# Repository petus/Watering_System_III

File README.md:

# Watering_System_III
Watering system with ESP8266 (ESP12E)

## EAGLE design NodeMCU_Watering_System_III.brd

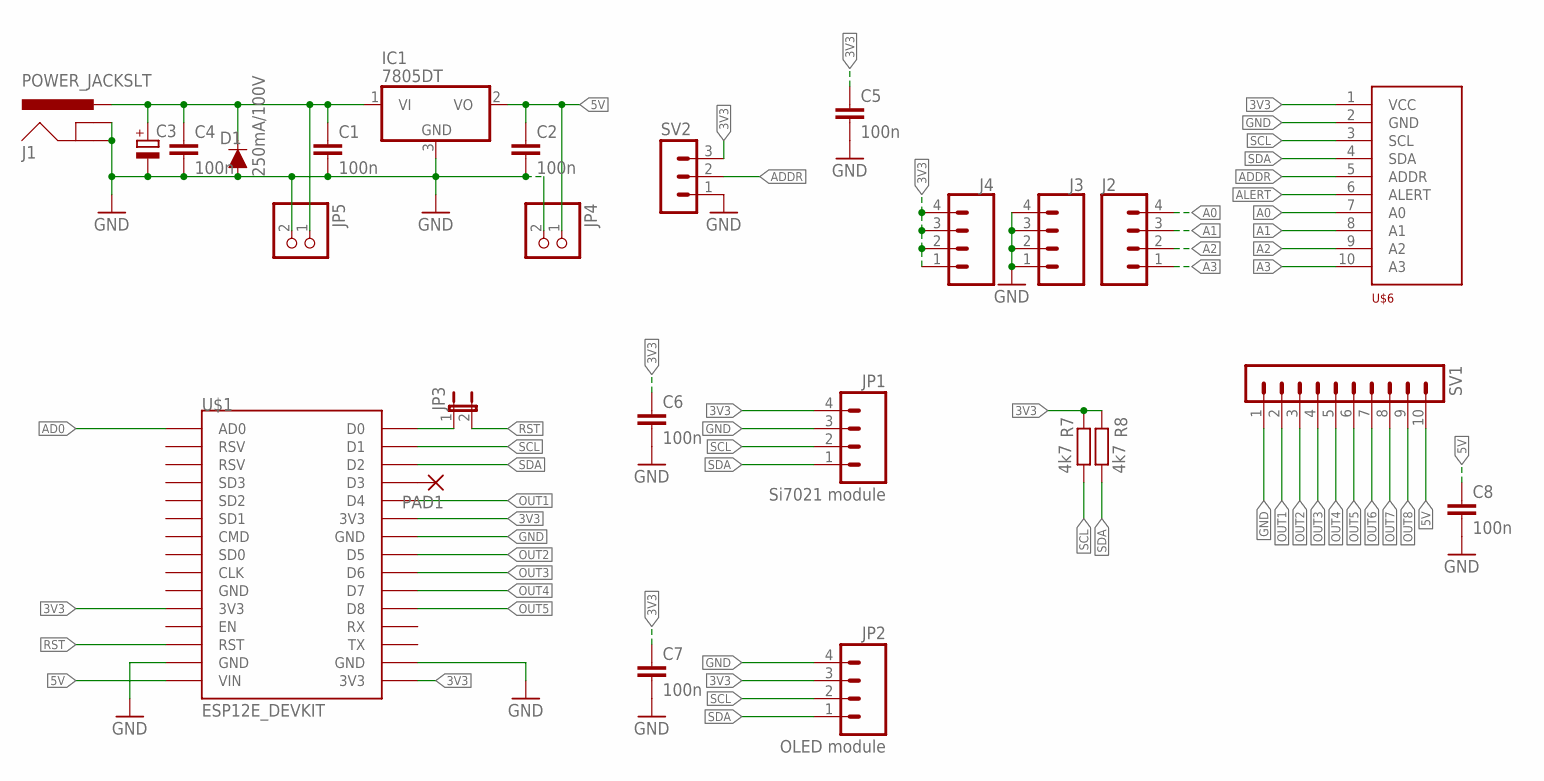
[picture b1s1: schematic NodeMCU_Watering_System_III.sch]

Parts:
C1, C2, C4, C5, C6, C7, C8: 100n; C0805K
C3: CPOL-EUB/3528-21W; B/3528-21W
D1: 250mA/100V; SOD-323
IC1: 7805DT; TO252
J1: POWER_JACKSLT; POWER_JACK_SLOT
J2, J3, J4: CONN_04; 1X04
JP1: Si7021 module; 1X04_LONGPADS
JP2: OLED module; 1X04_LONGPADS
JP3: JP1E; JP1
JP4, JP5: PINHD-1X2; 1X02
PAD1: 1,6/0,8
R7, R8: 4k7; M0805
SV1: MA10-1
SV2: MA03-1
U$1: ESP12E_DEVKIT
U$6: ADS1115_BOARD; ADS1115_ADS

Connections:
3V3: C5.1, C6.1, C7.1, J4.1, J4.2, J4.3, J4.4, JP1.4, JP2.3, R7.2, R8.2, SV2.3, U$1.3V3@0 (3V3), U$1.3V3@1 (3V3), U$1.3V3@2 (3V3), U$6.1 (VCC)
5V: C2.1, C8.1, IC1.2 (VO), JP4.1, SV1.10, U$1.VIN
A0: J2.4, U$6.7 (A0)
A1: J2.3, U$6.8 (A1)
A2: J2.2, U$6.9 (A2)
A3: J2.1, U$6.10 (A3)
AD0: U$1.AD0
ADDR: SV2.2, U$6.5 (ADDR)
ALERT: U$6.6 (ALERT)
GND: C1.2, C2.2, C3.-, C4.2, C5.2, C6.2, C7.2, C8.2, D1.A, IC1.3 (GND), J1.GND@1 (GNDBREAK), J1.GND@2 (GND), J3.1, J3.2, J3.3, J3.4, JP1.3, JP2.4, JP4.2, JP5.2, SV1.1, SV2.1, U$1.GND@1 (GND), U$1.GND@2 (GND), U$1.GND@3 (GND), U$6.2 (GND)
unnamed: JP3.1, U$1.D0
unnamed: PAD1.1, U$1.D3
OUT1: SV1.2, U$1.D4
OUT2: SV1.3, U$1.D5
OUT3: SV1.4, U$1.D6
OUT4: SV1.5, U$1.D7
OUT5: SV1.6, U$1.D8
OUT6: SV1.7
OUT7: SV1.8
OUT8: SV1.9
RST: JP3.2, U$1.RST
SCL: JP1.2, JP2.2, R7.1, U$1.D1, U$6.3 (SCL)
SDA: JP1.1, JP2.1, R8.1, U$1.D2, U$6.4 (SDA)
VIN: C1.1, C3.+, C4.1, D1.C, IC1.1 (VI), J1.PWR, JP5.1

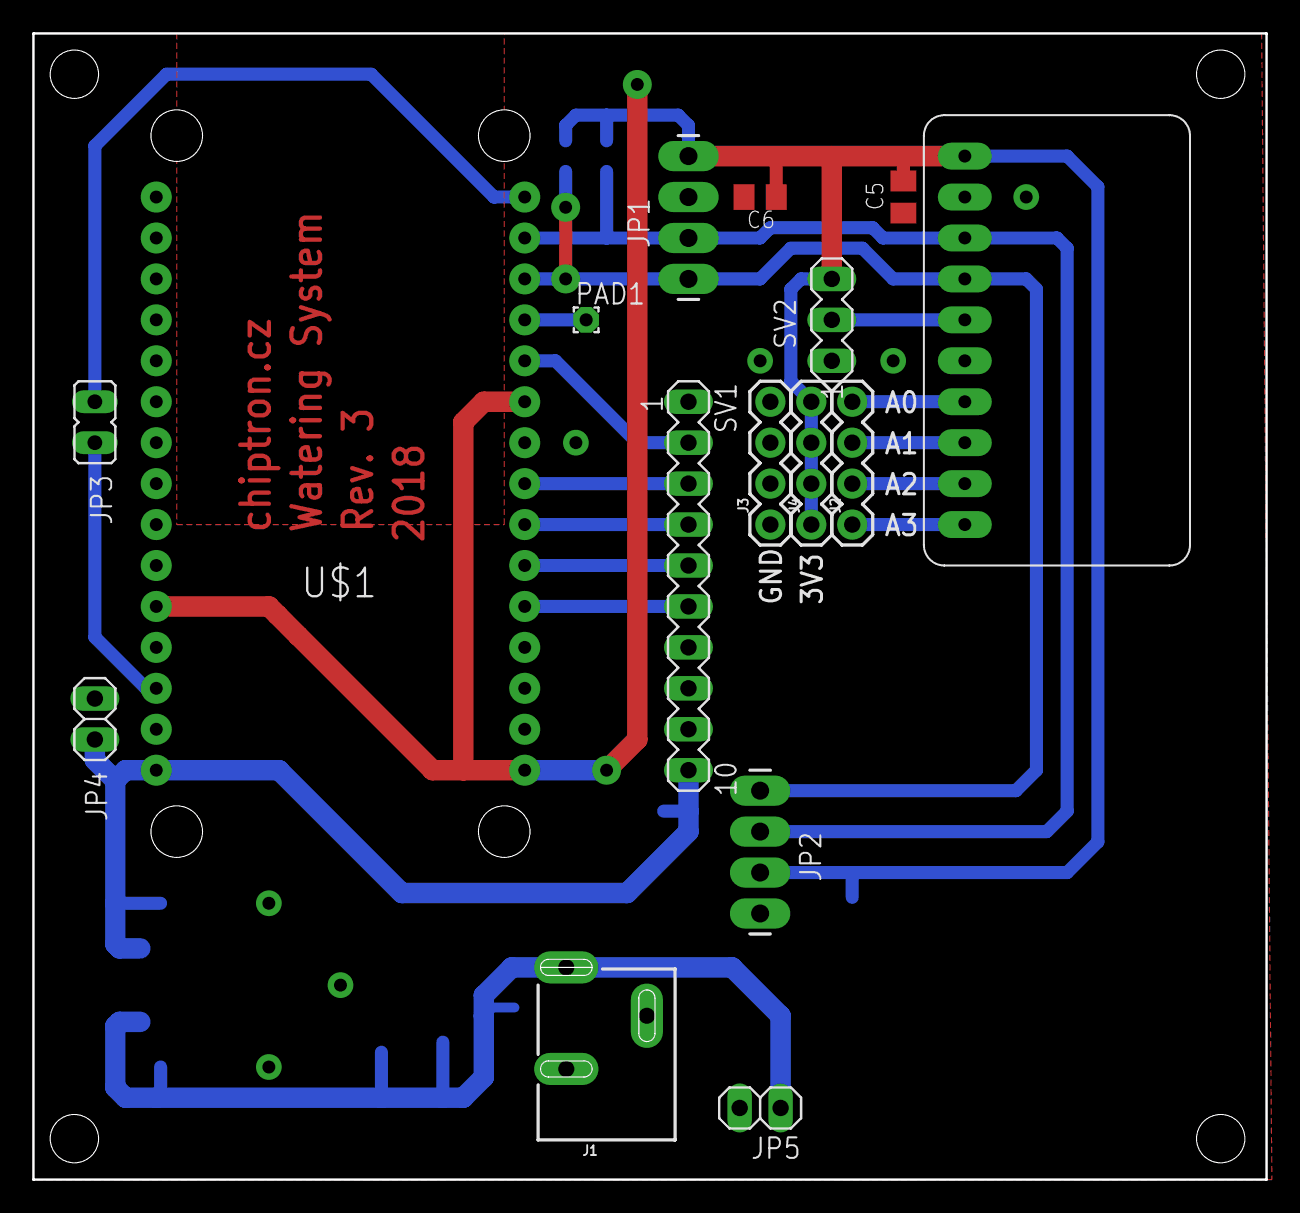
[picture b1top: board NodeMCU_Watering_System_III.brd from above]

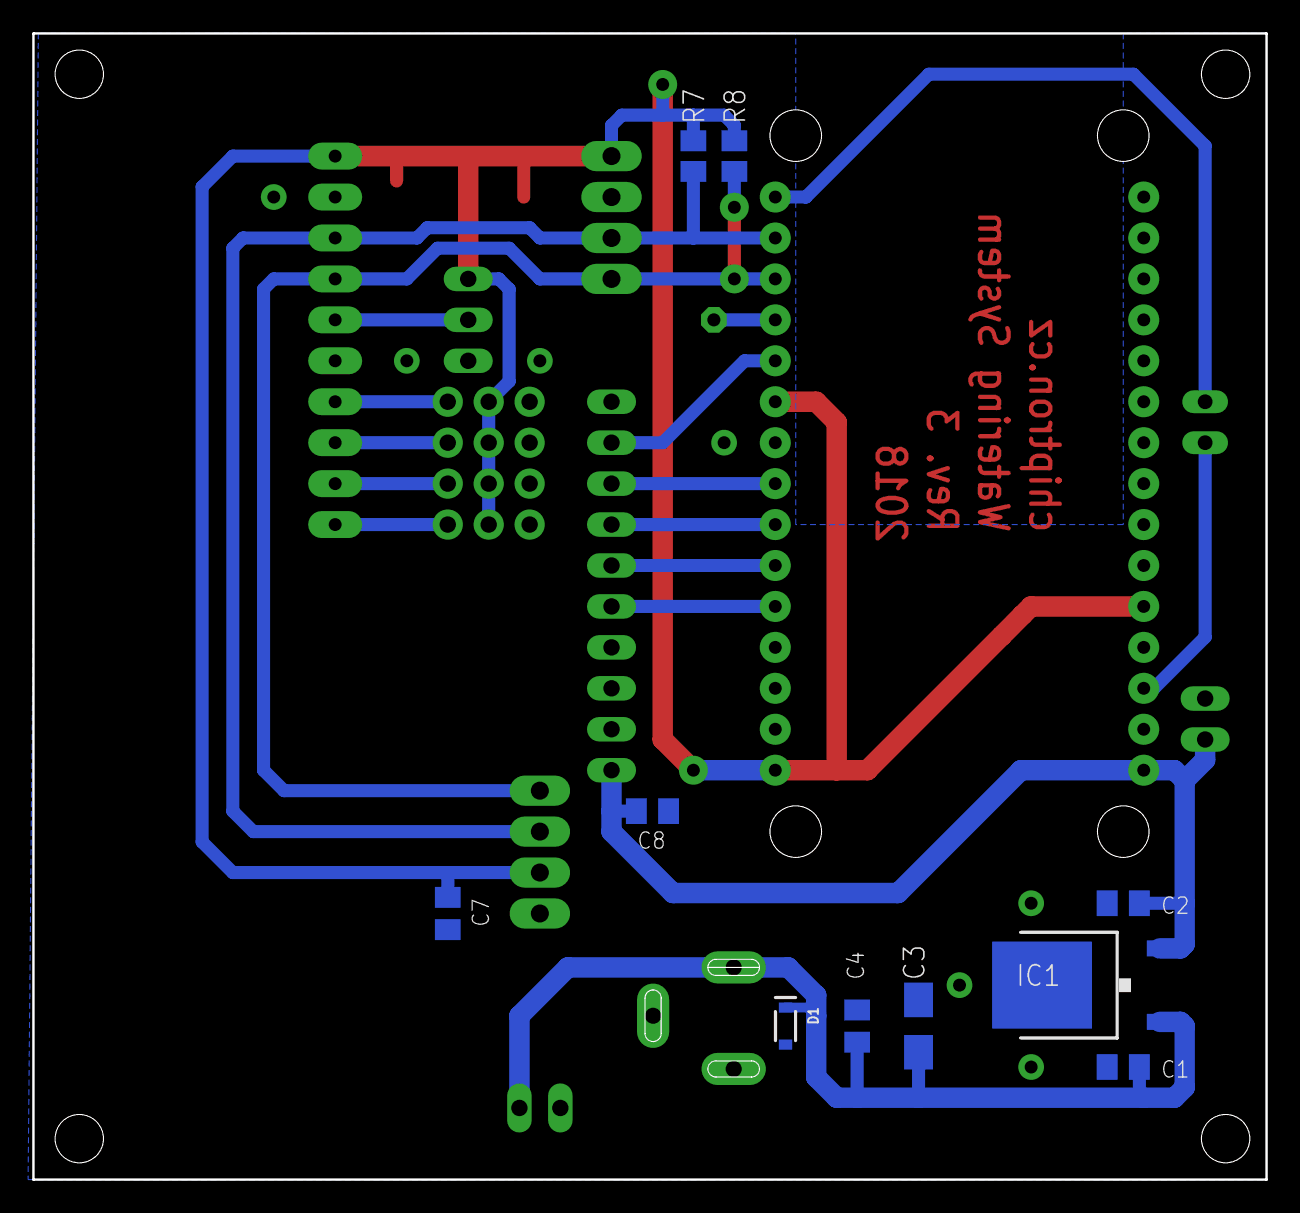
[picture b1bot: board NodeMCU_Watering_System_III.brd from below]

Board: 2 copper layers, 76.5 x 71.1 mm, 26 parts (10 on the bottom side), 19 nets.

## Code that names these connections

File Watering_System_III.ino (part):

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
const char* host = "HOSTNAME.tmep.cz";

#define PUMP  OUT1 
#define VALVE_1 OUT2 
#define VALVE_2 OUT3  
//#define VALVE_3 OUT4  
//#define VALVE_4 OUT5  

#define DBG_MSG		// Enable debug messages through UART
/* ---------------------------------------- */
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#define SCL 5 // GPIO5 on D1
#define OLED_RESET 19 //choose unused pin, connect the RESET pin to VCC (3.3V)

#define OUT1  2 //GPIO2 on D4
#define OUT2 14 //GPIO14 on D5
#define OUT3 12  //GPIO12 on D6
#define OUT4 13  //GPIO13 on D7
#define OUT5 15  //GPIO15 on D8

#ifdef USE_OLED
    Adafruit_SSD1306 display(OLED_RESET);
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

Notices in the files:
parts and their libraries:
SparkFun: Licensing: CC v3.0 Share-Alike You are welcome to use this library for commercial purposes.
SparkFun-Connectors: Licensing: Creative Commons ShareAlike 4.0 International - https://creativecommons.org/licenses/by-sa/4.0
